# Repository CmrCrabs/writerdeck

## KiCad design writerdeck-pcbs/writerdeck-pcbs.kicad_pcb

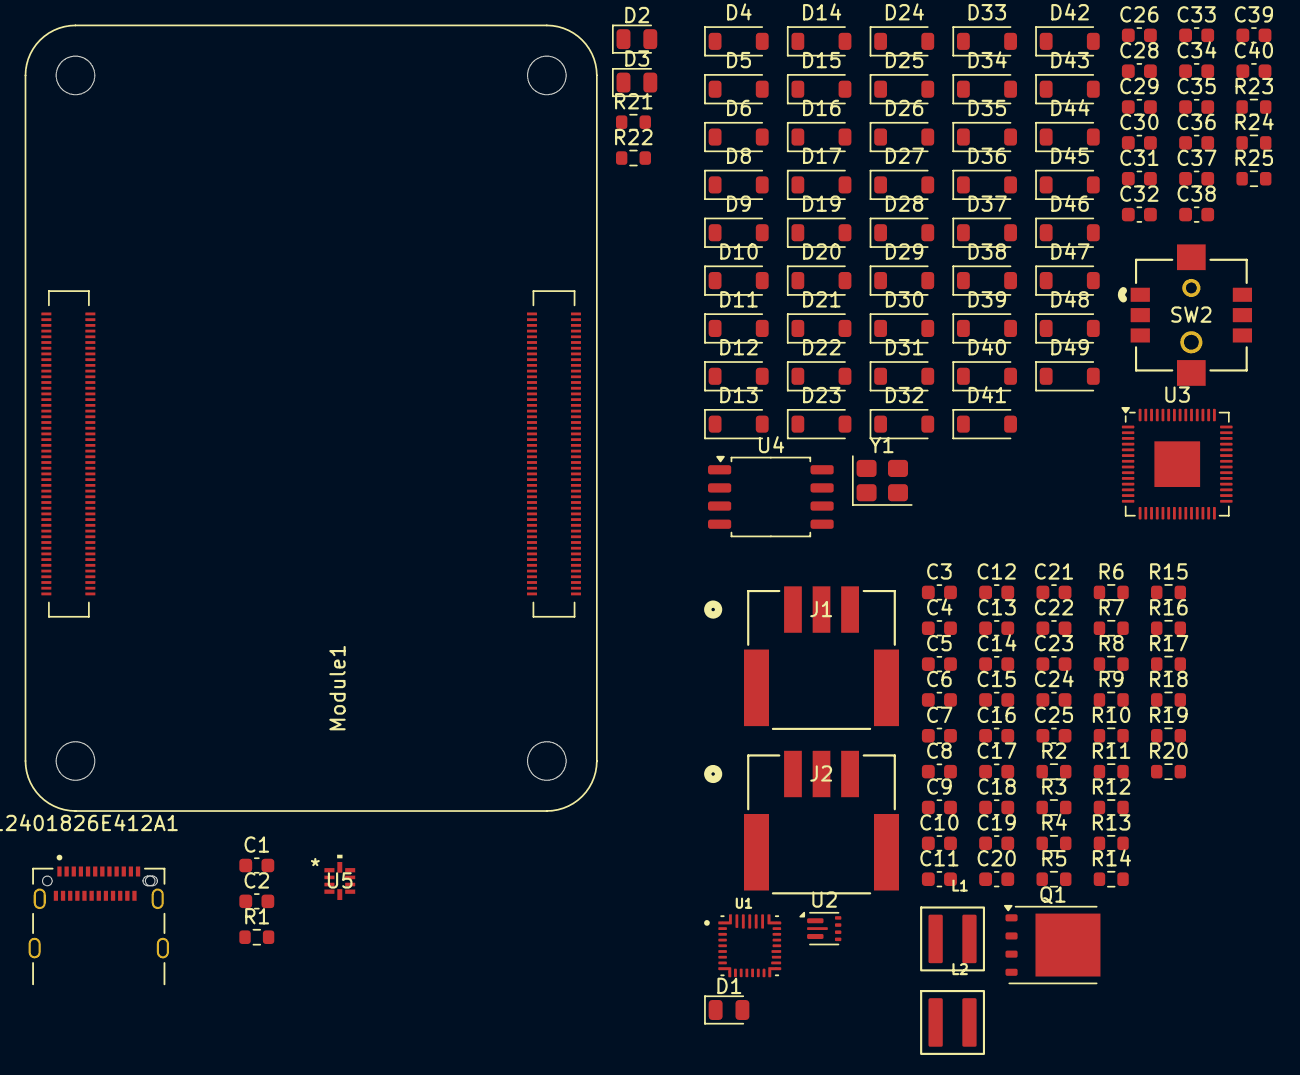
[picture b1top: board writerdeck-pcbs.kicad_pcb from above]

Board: 2 copper layers, 125 parts (0 on the bottom side), 64 nets, no tracks yet.

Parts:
C1, C2, C5, C6, C7, C26, C31, C32, C33, C34, C36, C37, C38, C39, C40: 100n; C_0603_1608Metric
C3, C4, C8, C9, C10, C11, C12, C13, C15, C16, C17, C18, C21: 10u; C_0603_1608Metric
C14: 2u2; C_0603_1608Metric
C19, C20: 47n; C_0603_1608Metric
C22: 4u7; C_0603_1608Metric
C23, C24, C25: 22u; C_0603_1608Metric
C28, C30: 22p; C_0603_1608Metric
C29, C35: 1u; C_0603_1608Metric
D1: Blue LED; LED_0805_2012Metric
D2: Red LED; LED_0805_2012Metric
D3: Green LED; LED_0805_2012Metric
D4, D5, D6, D8, D9, D10, D11, D12, D13, D14, D15, D16, D17, D19, D20, D21, D22, D23, D24, D25, D26, D27, D28, D29, D30, D31, D32, D33, D34, D35, D36, D37, D38, D39, D40, D41, D42, D43, D44, D45, D46, D47, D48, D49: 1N4148W-TP; D_SOD-123
J1, J2: 5023520300
J12401826E412A1: USB_C_Receptacle; 12401826E412A
L1, L2: 1u; XFL4020-102MEC
Module1: ComputeModule5-CM5; Raspberry-Pi-5-Compute-Module
Q1: CSD17570Q5B; TDSON-8-1
R1, R19: 2k2; R_0603_1608Metric
R2, R9: 100R; R_0603_1608Metric
R3, R4, R5, R11, R13, R16: 10k; R_0603_1608Metric
R6: 2k; R_0603_1608Metric
R7: 620R; R_0603_1608Metric
R8: 15k; R_0603_1608Metric
R10: 50R; R_0603_1608Metric
R12: 2R; R_0603_1608Metric
R14, R18: 100k; R_0603_1608Metric
R15: 300k; R_0603_1608Metric
R17: 732k; R_0603_1608Metric
R20: 3k; R_0603_1608Metric
R21, R22, R23: 1k; R_0603_1608Metric
R24, R25: 27R; R_0603_1608Metric
SW2: SKRHABE010
U1: BQ25792RQMR
U2: TPS61022RWUR; Texas_RWU0007A_VQFN-7_2x2mm_P0.5mm
U3: RP2040; QFN-56-1EP_7x7mm_P0.4mm_EP3.2x3.2mm
U4: W25Q16JVSS; SOIC-8_5.3x5.3mm_P1.27mm
U5: TS3USB221ERSER
Y1: X322512MSB4SI; Crystal_SMD_3225-4Pin_3.2x2.5mm

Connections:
/CM5 GPIO/+3.3v: C26.1, C29.1, C31.1, C32.1, C33.1, C34.1, C36.1, C38.1, C39.1, D2.2 (A), D3.2 (A), Module1.84 (+3.3v_(Output)), Module1.86 (+3.3v_(Output)), U3.1 (IOVDD), U3.10 (IOVDD), U3.22 (IOVDD), U3.33 (IOVDD), U3.42 (IOVDD), U3.43 (ADC_AVDD), U3.44 (VREG_IN), U3.48 (USB_VDD), U3.49 (IOVDD), U4.8 (VCC)
/CM5 GPIO/+5v: C23.1, C24.1, C25.1, Module1.77 (+5v_(Input)), Module1.79 (+5v_(Input)), Module1.81 (+5v_(Input)), Module1.83 (+5v_(Input)), Module1.85 (+5v_(Input)), Module1.87 (+5v_(Input)), R17.1, U2.3 (VOUT)
/CM5 GPIO/CC1: J12401826E412A1.A5 (CC1), Module1.94 (CC1)
/CM5 GPIO/CC2: J12401826E412A1.B5 (CC2), Module1.96 (CC2)
/CM5 GPIO/LED_nACT: Module1.21 (LED_nACT), R22.2
/CM5 GPIO/LED_nPWR: Module1.95 (LED_nPWR), R21.2
/CM5 GPIO/PMIC_INT: Module1.58 (GPIO2), R11.1
/CM5 GPIO/SWCLK: Module1.54 (GPIO4), U3.24 (SWCLK)
/CM5 GPIO/SWD: Module1.56 (GPIO3), U3.25 (SWD)
/CM5 Highspeed/USB2_N: J12401826E412A1.A7 (D-), J12401826E412A1.B7 (D-), U1.7 (D-), U5.7 (D-)
/CM5 Highspeed/USB2_P: J12401826E412A1.A6 (D+), J12401826E412A1.B6 (D+), U1.6 (D+), U5.8 (D+)
/Keyboard/+1v1: C35.1, C37.1, C40.1, U3.23 (DVDD), U3.45 (VREG_VOUT), U3.50 (DVDD)
/Keyboard/CS: R23.2, U3.56 (QSPI_SS), U4.1 (~CS)
/Keyboard/LMB: SW2.2, U3.18 (GPIO15)
/Keyboard/MOUSE_A: SW2.1, U3.38 (GPIO26_ADC0)
/Keyboard/MOUSE_B: SW2.4, U3.39 (GPIO27_ADC1)
/Keyboard/MOUSE_C: SW2.3, U3.40 (GPIO28_ADC2)
/Keyboard/MOUSE_D: SW2.6, U3.41 (GPIO29_ADC3)
/Keyboard/ROW1: D4.1 (K), D5.1 (K), D6.1 (K), D13.1 (K), D14.1 (K), D15.1 (K), D16.1 (K), D17.1 (K), U3.13 (GPIO10)
/Keyboard/ROW2: D8.1 (K), D9.1 (K), D10.1 (K), D11.1 (K), D12.1 (K), D19.1 (K), D20.1 (K), D21.1 (K), D22.1 (K), D23.1 (K), U3.14 (GPIO11)
/Keyboard/ROW3: D24.1 (K), D25.1 (K), D26.1 (K), D27.1 (K), D28.1 (K), D29.1 (K), D30.1 (K), D31.1 (K), D32.1 (K), D33.1 (K), U3.15 (GPIO12)
/Keyboard/ROW4: D34.1 (K), D35.1 (K), D36.1 (K), D37.1 (K), D38.1 (K), D39.1 (K), D40.1 (K), D41.1 (K), D42.1 (K), D43.1 (K), U3.16 (GPIO13)
/Keyboard/ROW5: D44.1 (K), D45.1 (K), D46.1 (K), D47.1 (K), D48.1 (K), D49.1 (K), U3.17 (GPIO14)
/Keyboard/SD0: U3.53 (QSPI_SD0), U4.5 (DI(IO_{0}))
/Keyboard/SD1: U3.55 (QSPI_SD1), U4.2 (DO(IO_{1}))
/Keyboard/SD2: U3.54 (QSPI_SD2), U4.3 (~WP(IO_{2}))
/Keyboard/SD3: U3.51 (QSPI_SD3), U4.7 (~RST(IO_{3}))
/Keyboard/SD_CLK: U3.52 (QSPI_SCLK), U4.6 (CLK)
/Keyboard/USB_DN: R25.2, U3.46 (USB_DM)
/Keyboard/USB_DP: R24.2, U3.47 (USB_DP)
/Keyboard/XTAL_IN: C28.1, U3.20 (XIN), Y1.1
/Power Management/BAT: C3.1, C4.1, Q1.5 (D), U1.22 (BAT), U1.23 (BAT__1)
/Power Management/BATP: R2.1, U1.18 (BATP)
/Power Management/BATT_TEMP: J1.2, J2.2, R7.2, R8.1, U1.16 (TS)
/Power Management/BTST1: C19.1, U1.4 (BTST1)
/Power Management/BTST2: C20.2, U1.19 (BTST2)
/Power Management/ILIM_HIZ: R14.2, R15.1, U1.17 (ILIM_HIZ)
/Power Management/PROG: R20.1, U1.20 (PROG)
/Power Management/QON: Module1.92 (PWR_BUT), R16.2, U1.12 (~QON)
/Power Management/REGN: C22.1, R6.1, R14.1, R16.1, R19.1, U1.5 (REGN)
/Power Management/SCL: R3.2, U1.14 (SCL)
/Power Management/SDA: R4.1, U1.15 (SDA)
/Power Management/SDRV: Q1.4 (G), U1.24 (SDRV)
/Power Management/STAT: D1.1 (K), U1.1 (STAT)
/Power Management/SW1: C19.2, L2.1, U1.28 (SW1)
/Power Management/SW2: C20.1, L2.2, U1.26 (SW2)
/Power Management/VBUS: C1.1, C2.1, C5.1, C8.1, C11.1, J12401826E412A1.A4 (VBUS), J12401826E412A1.A9 (VBUS), J12401826E412A1.B4 (VBUS), J12401826E412A1.B9 (VBUS), R1.1, R12.1, U1.2 (VBUS), U1.3 (VBUS__1), U1.8 (VAC2), U1.9 (VAC1)
/Power Management/VSYS: C7.1, C10.1, C13.1, C16.1, C17.1, C18.1, C21.1, L1.1, R13.1, U1.25 (SYS), U2.7 (VIN)
GND: C1.2, C2.2, C3.2, C4.2, C5.2, C6.2, C7.2, C8.2, C9.2, C10.2, C11.2, C12.2, C13.2, C14.2, C15.2, C16.2, C17.2, C18.2, C21.2, C22.2, C23.2, C24.2, C25.2, C26.2, C28.2, C29.2, C30.2, C31.2, C32.2, C33.2, C34.2, C35.2, C36.2, C37.2, C38.2, C39.2, C40.2, J1.3, J2.3, J12401826E412A1.A1 (GND), J12401826E412A1.A12 (GND), J12401826E412A1.B1 (GND), J12401826E412A1.B12 (GND), R1.2, R5.1, R10.2, R15.2, R18.2, R20.2, SW2.5, U1.10 (ACDRV2), U1.11 (ACDRV1), U1.27 (GND), U2.1 (GND), U3.19 (TESTEN), U3.57 (GND), U4.4 (GND), Y1.2, Y1.4
unnamed: C14.1, R12.2
unnamed: C30.1, Y1.3
unnamed: D1.2 (A), R19.2
unnamed: D2.1 (K), R21.1
unnamed: D3.1 (K), R22.1
unnamed: R6.2, R7.1
unnamed: R8.2, R9.1
unnamed: R9.2, R10.1
unnamed: C6.1, C9.1, C12.1, C15.1, U1.29 (PMID)
unnamed: R5.2, U1.13 (~CE)
unnamed: R11.2, U1.21 (~INT)
unnamed: R13.2, U2.5 (EN), U2.6 (MODE)
unnamed: R17.2, R18.1, U2.4 (FB)
unnamed: L1.2, U2.2 (SW)
V_BATT: J1.1, J2.1, Q1.1 (S), Q1.2 (S), Q1.3 (S), R2.2

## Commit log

2026-01-24 pmic start, structure
2026-02-25 power management done
2026-03-03 pre switch matrix, restructure
2026-03-03 rm backups
2026-03-12 backup

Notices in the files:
parts and their libraries:
License: Apache-2.0
